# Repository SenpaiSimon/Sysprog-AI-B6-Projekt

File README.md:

# Sysprog-AI-B6-Projekt

## Entwickler:  
- Anton Kraus
- Simon Obermeier

---

## Referenz 

Dieses Projekt wurde im Rahmen einer Studienarbeit für das Modul **"Systemprogrammierung"** an der Technischen Hochschule Deggendorf im Studiengang **Angewandte Informatik** des 6. Semesters, angelegt. 

---

## Kurzbeschreibung

Dieses Projekt beinhaltet das schreiben eines **Linux Kernel Drivers** für einen **Raspberry PI 4** und eine dazugehörige **User-App**.  
Diese sollen eine **8 * 8 LED-Matrix** ansteuern.   
Weitere Infos dazu werden in der schriftlichen Ausarbeitung des Projekts behandelt.

---

## How to use 

Um die den das Module zu installieren müssen zunächst die Linux Kernel Treiber installiert werden mit dem Befehlen: 
> sudo apt-get install linux-headers-$(uname -r)  
> sudo apt-get upgrade  
> sudo reboot

Danach kann das einfache install-script unter:
> /src/install

ausgeführt werden mit dem Befehl:

> bash install_compile.sh

Dies kompiliert das Kernel Module, installiert es in den Kernel, kompiliert die User-App und startet diese. 

---

### Start User App

Die User App liegt dann unter
> /src/user_app

und kann mit dem Kommando: 
> ./app

ausgeführt werden.

---

### Live Kamera Feed

Um die Matrix Remote zu betrachten wurde ein Script eingerichtet um das Live-Bild der Kamera an einen lokale IP-Adresse zu streamen.

Das Skript liegt unter
> /src/install/

und kann mit:
> bash start_camera_feed.sh

gestartet werden.

Danach kann man auf die angezeigten Hostnamen mit (z.B.) VLC Media Player zugreifen.

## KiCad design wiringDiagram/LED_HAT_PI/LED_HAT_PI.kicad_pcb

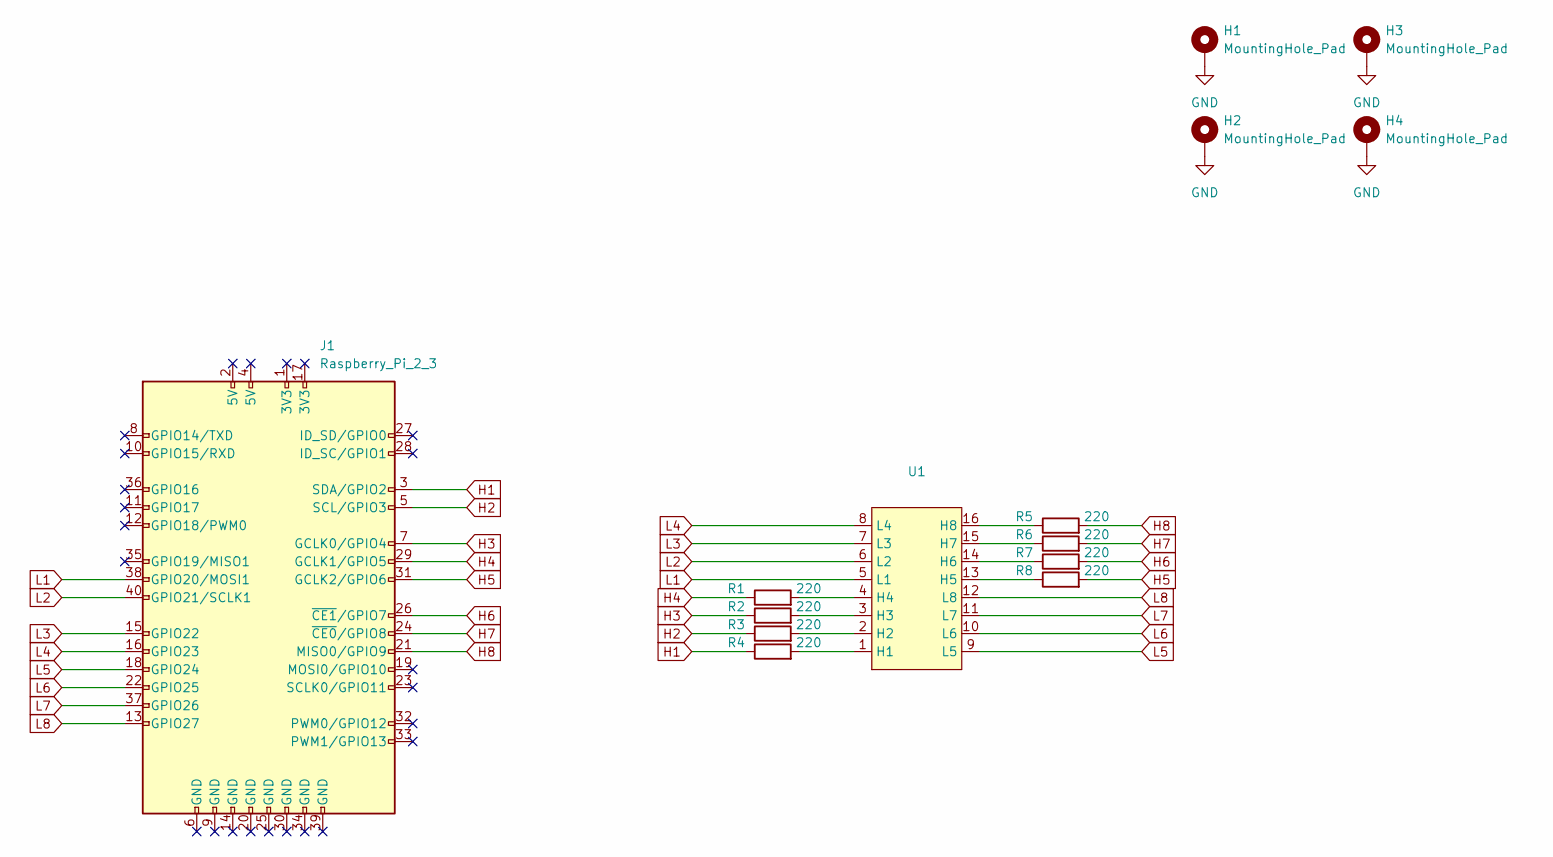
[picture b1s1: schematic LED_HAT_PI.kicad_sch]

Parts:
H1, H2, H3, H4: MountingHole_Pad; MountingHole_3.2mm_M3_Pad_Via
J1: Raspberry_Pi_2_3; PinSocket_2x20_P2.54mm_Vertical
R1, R2, R3, R4, R5, R6, R7, R8: 220; R_0603_1608Metric
U1: (no value)

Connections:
GND: H1.1, H2.1, H3.1, H4.1
H1: J1.3 (SDA/GPIO2), R4.1
H2: J1.5 (SCL/GPIO3), R3.1
H3: J1.7 (GCLK0/GPIO4), R2.1
H4: J1.29 (GCLK1/GPIO5), R1.1
H5: J1.31 (GCLK2/GPIO6), R8.2
H6: J1.26 (~CE1/GPIO7), R7.2
H7: J1.24 (~CE0/GPIO8), R6.2
H8: J1.21 (MISO0/GPIO9), R5.2
L1: J1.38 (GPIO20/MOSI1), U1.5 (L1)
L2: J1.40 (GPIO21/SCLK1), U1.6 (L2)
L3: J1.15 (GPIO22), U1.7 (L3)
L4: J1.16 (GPIO23), U1.8 (L4)
L5: J1.18 (GPIO24), U1.9 (L5)
L6: J1.22 (GPIO25), U1.10 (L6)
L7: J1.37 (GPIO26), U1.11 (L7)
L8: J1.13 (GPIO27), U1.12 (L8)
unnamed: R1.2, U1.4 (H4)
unnamed: R2.2, U1.3 (H3)
unnamed: R3.2, U1.2 (H2)
unnamed: R4.2, U1.1 (H1)
unnamed: R5.1, U1.16 (H8)
unnamed: R6.1, U1.15 (H7)
unnamed: R7.1, U1.14 (H6)
unnamed: R8.1, U1.13 (H5)

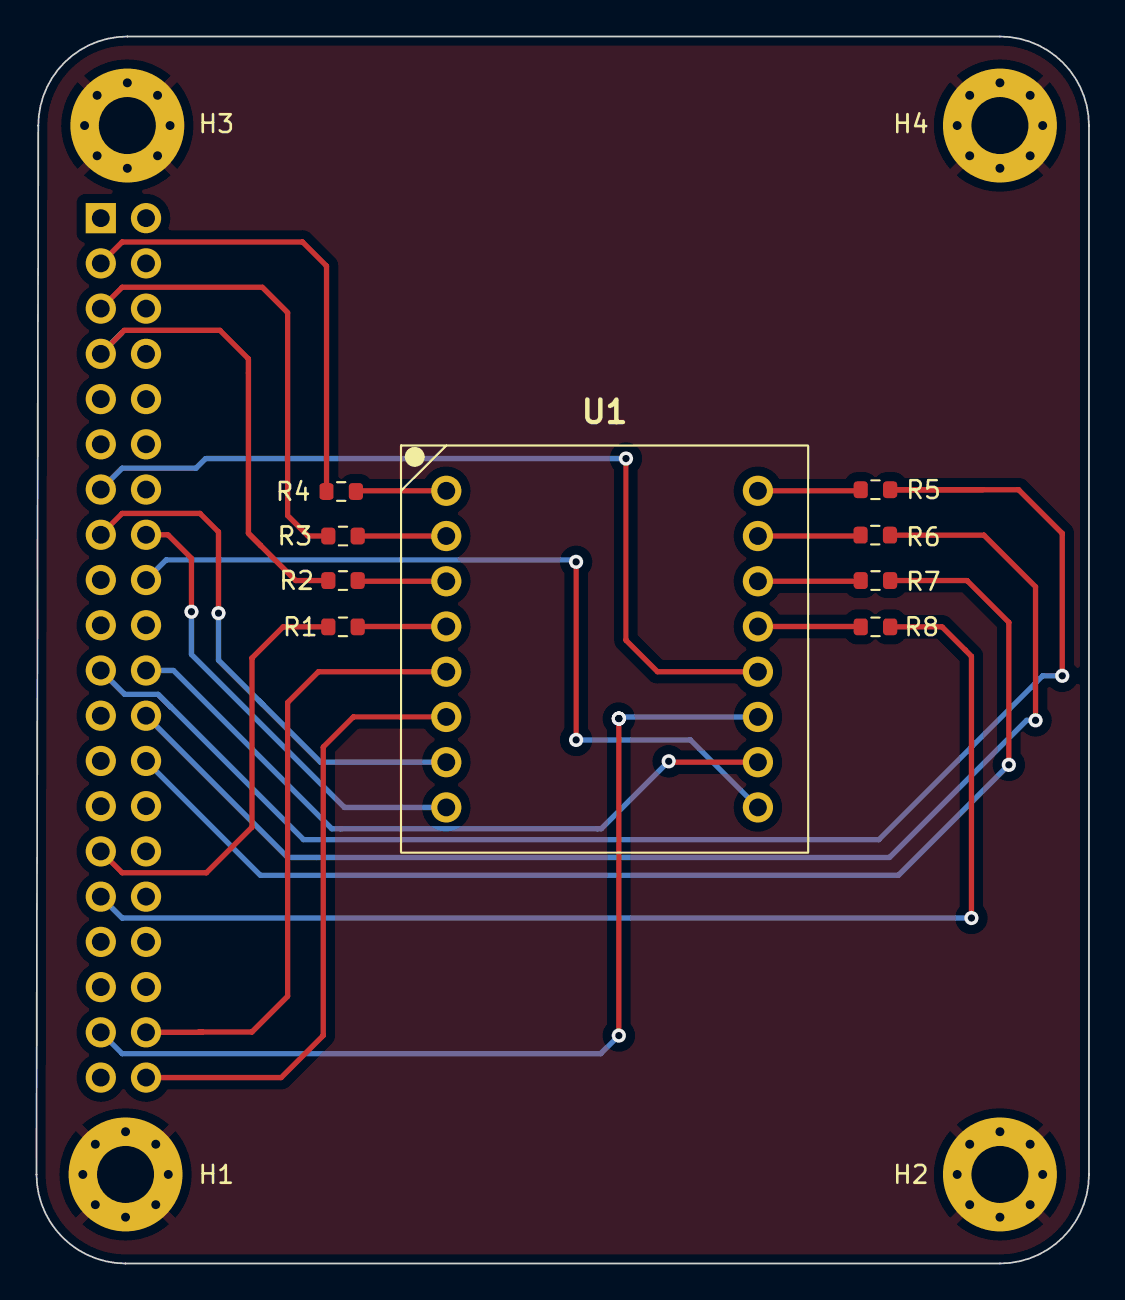
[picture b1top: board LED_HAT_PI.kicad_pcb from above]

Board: 2 copper layers, 59.1 x 68.9 mm, 14 parts (1 on the bottom side), 25 nets.

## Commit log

2022-05-04 Added structure
2022-05-04 Added Code Baseline and split files into headers
2022-05-04 Added pinout picture
2022-05-04 Added startup init code for GPIOS with checks
2022-05-04 Comments added to everything and added Kernel Prints
2022-05-04 Comments and moved IOCT Commands to header
2022-05-04 Include Defines Changed
2022-05-05 Added install skript and changed file structure
2022-05-05 Added controller
2022-05-05 Expanded to 8 pins per side
2022-05-09 Added Camera Control
2022-05-10 Fixed controlling of the LEDs
2022-05-10 Dont ask
2022-05-11 WIP Printout
2022-05-11 It works
2022-05-11 Better Output Layout
2022-05-11 Driver done
2022-05-11 Started user app
2022-05-11 Started LED functions
2022-05-11 User App Done
2022-05-12 User app extended, fixed devWrite bug
2022-05-12 Changed logs dir
2022-05-12 Readme
2022-05-12 Added Schematic and started doc
2022-05-19 init doku
2022-05-28 continued with doc
2022-05-30 finished pi hat
    added finished pi hat from external project (safety reasons)
2022-05-30 fixed my name, fixed order, fixed redunant sources
2022-06-09 rough structure of documentation
2022-06-11 Continued on documeantation
2022-06-11 Fixed library paths
2022-06-12 finished rough documentation
    TBD User App Steuerung und Inhaltsverzeichnis fixen
2022-06-12 forgot to save
2022-06-14 Fixed install script
2022-06-14 doc bump
2022-06-14 Strcuture changed
2022-06-15 Small changes
2022-06-23 Moved source code to the end
2022-06-23 Added references for code
2022-06-23 rewritten a lot of doc
2022-06-23 extended doc, see continue
2022-06-24 KErnel doc done
2022-06-25 Doc done - see problems at the end
2022-06-25 typo
2022-06-25 Korrektur die Erste
2022-06-25 Update References
2022-06-25 Kommasetzung ist schwer
2022-06-26 documentation
    worked on documentation for better readability
2022-06-29 Include path nightmare
2022-07-01 added sign
2022-07-01 Revert "Merge branch 'main' of https://github.com/SenpaiSimon/Sysprog-AI-B6-Projekt"
    This reverts commit 40f50e02f7d8b7f58dd1fc93ef2fc5bb93a9ac1d, reversing
    changes made to b7071fd859b3df6c3cba2f2d9c9308c2bdeae55d.
2022-07-01 Revert "added sign"
    This reverts commit b7071fd859b3df6c3cba2f2d9c9308c2bdeae55d.
2022-07-01 sign
2022-07-01 multiplex
2022-07-01 doku done
2022-07-03 Added Signiture
    Added my Signiture to Erklärung and corrected one komma
2022-07-04 Erklärung done
2022-07-05 signage line
2022-07-07 small fix
2022-07-07 recompiled app
2022-07-07 intellisense stuff
2022-07-07 small change in doku
2022-07-08 added pdf
